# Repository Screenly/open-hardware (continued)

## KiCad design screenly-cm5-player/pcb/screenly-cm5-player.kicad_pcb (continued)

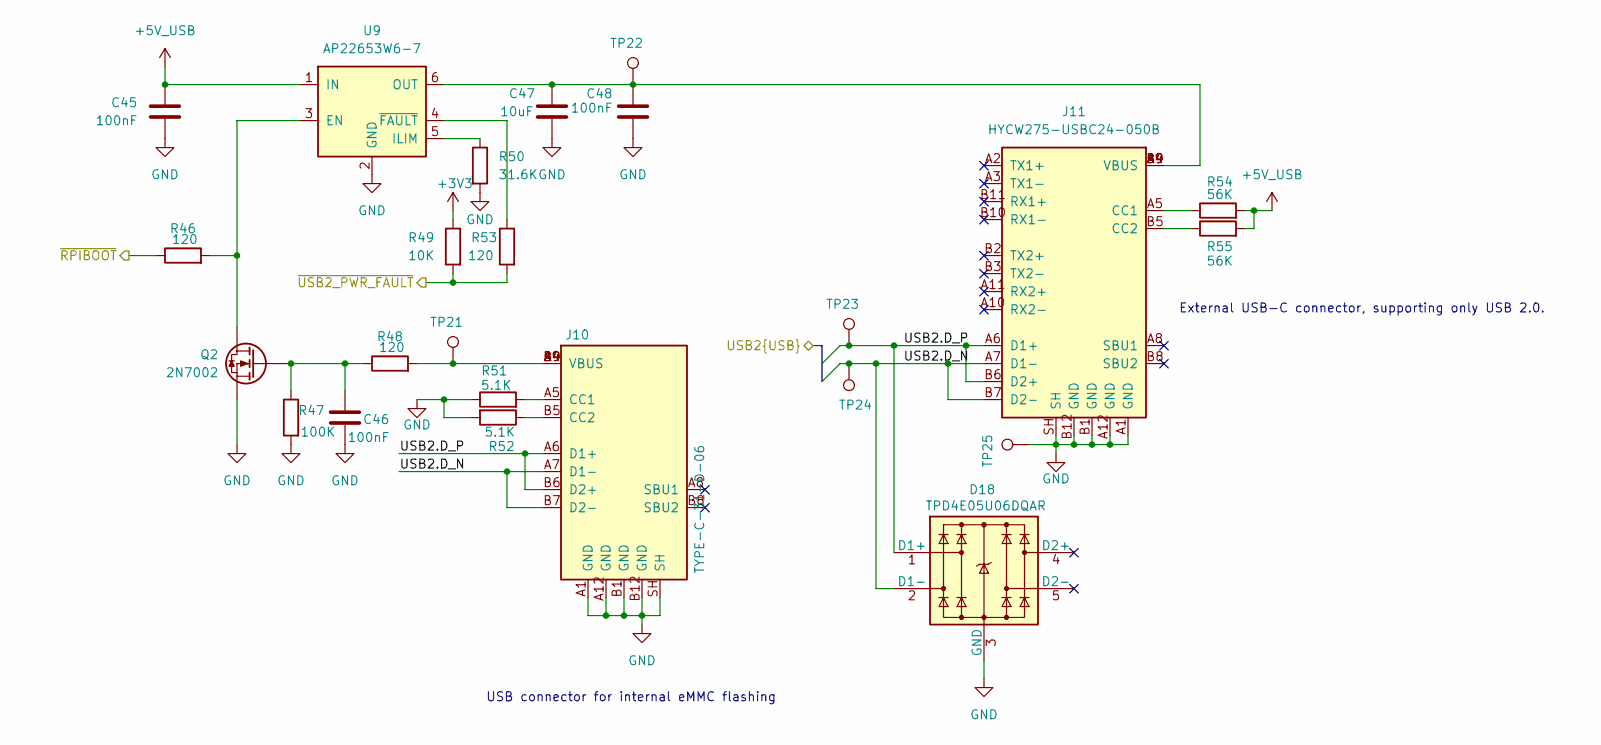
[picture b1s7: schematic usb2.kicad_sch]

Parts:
C45, C46, C48: 100nF; C_0402; tolerance 10%; voltage 50V; PartNumber SRLY-CAP-000001
C47: 10uF; C_1210; tolerance 10%; voltage 50V; PartNumber SRLY-CAP-000002
D18: TPD4E05U06DQAR; TI_USON-10_2.5x1.0mm_P0.5mm; PartNumber SRLY-DIO-000004
J10: TYPE-C-31-D-06; USB_C_Receptacle_HRO_TYPE-C-31-D-06_Vertical; voltage 5V; PartNumber SRLY-CON-000010
J11: HYCW275-USBC24-050B; USB_C_Receptacle_HOAUC_HYCW275-USBC24-050B; PartNumber SRLY-CON-000009
Q2: 2N7002; SOT-23; PartNumber SRLY-FET-000002
R46, R48, R53: 120; R_0402; tolerance 5%; voltage 50V; PartNumber SRLY-RES-000009
R47: 100K; R_0402; tolerance 1%; voltage 50V; PartNumber SRLY-RES-000004
R49: 10K; R_0402; tolerance 1%; voltage 50V; PartNumber SRLY-RES-000005
R50: 31.6K; R_0402; tolerance 1%; voltage 50V; PartNumber SRLY-RES-000010
R51, R52: 5.1K; R_0402; tolerance 1%; voltage 50V; PartNumber SRLY-RES-000012
R54, R55: 56K; R_0402; tolerance 1%; voltage 50V; PartNumber SRLY-RES-000013
TP21, TP22, TP23, TP24, TP25: TestPoint; TestPoint_Pad_D2.0mm
U9: AP22653W6-7; SOT-23-6; PartNumber SRLY-PWR-000003

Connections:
+3V3: R49.1; also elsewhere on the board
+5V_USB: C45.1, R54.2, R55.2, U9.1 (IN); also elsewhere on the board
/Compute Module/USB2.D_N: D18.2 (D1-), D18.9, J10.A7 (D1-), J10.B7 (D2-), J11.A7 (D1-), J11.B7 (D2-), TP24.1 (1_1); also elsewhere on the board
/Compute Module/USB2.D_P: D18.1 (D1+), D18.10, J10.A6 (D1+), J10.B6 (D2+), J11.A6 (D1+), J11.B6 (D2+), TP23.1 (1_1); also elsewhere on the board
/Compute Module/~RPIBOOT: R46.1; also elsewhere on the board
/Compute Module/~USB2_PWR_FAULT: R49.2, R53.2; also elsewhere on the board
GND: C45.2, C46.2, C47.2, C48.2, D18.3 (GND), D18.8 (GND), J10.A1 (GND), J10.A12 (GND), J10.B1 (GND), J10.B12 (GND), J10.SH, J11.A1 (GND), J11.A12 (GND), J11.B1 (GND), J11.B12 (GND), J11.SH, Q2.2 (S), R47.2, R50.2, R51.1, R52.2, TP25.1 (1_1), U9.2 (GND); also elsewhere on the board
unnamed: J10.A5 (CC1), R51.2
unnamed: J10.B5 (CC2), R52.1
unnamed: J10.A4 (VBUS), J10.A9 (VBUS), J10.B4 (VBUS), J10.B9 (VBUS), R48.2, TP21.1 (1_1)
unnamed: J11.A5 (CC1), R54.1
unnamed: J11.B5 (CC2), R55.1
unnamed: Q2.3 (D), R46.2, U9.3 (EN)
unnamed: C46.1, Q2.1 (G), R47.1, R48.1
unnamed: R50.1, U9.5 (ILIM)
unnamed: C47.1, C48.1, J11.A4 (VBUS), J11.A9 (VBUS), J11.B4 (VBUS), J11.B9 (VBUS), TP22.1 (1_1), U9.6 (OUT)
unnamed: R53.1, U9.4 (~FAULT)

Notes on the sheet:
External USB-C connector, supporting only USB 2.0.
USB connector for internal eMMC flashing

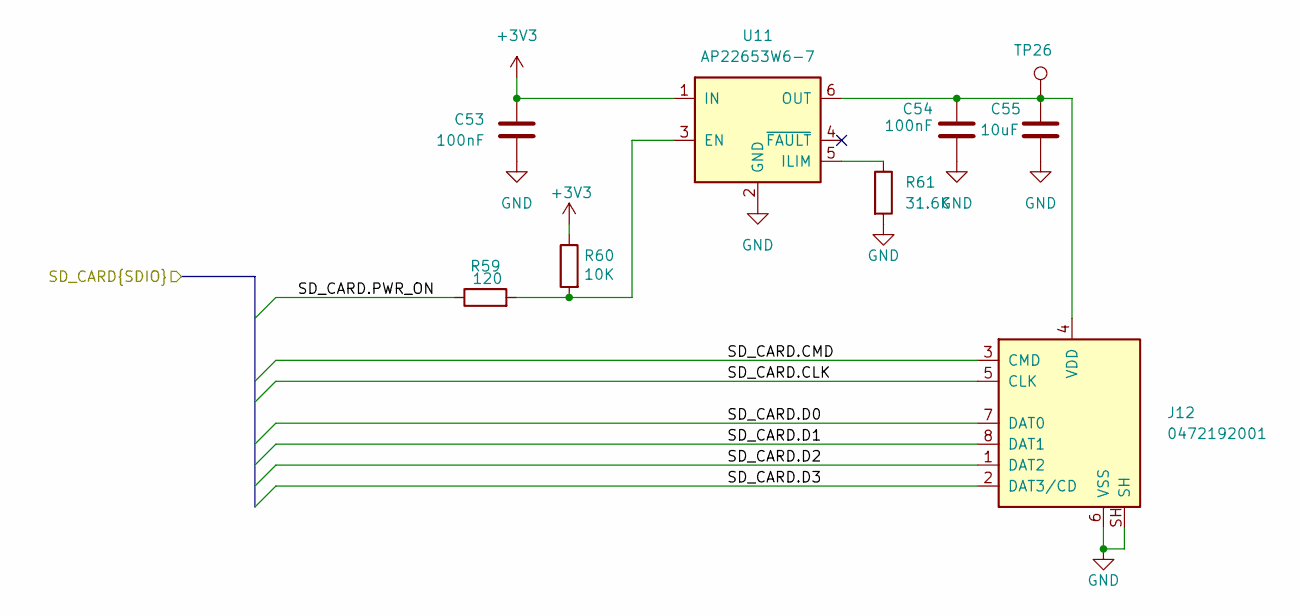
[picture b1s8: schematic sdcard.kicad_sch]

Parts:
C53, C54: 100nF; C_0402; tolerance 10%; voltage 50V; PartNumber SRLY-CAP-000001
C55: 10uF; C_1210; tolerance 10%; voltage 50V; PartNumber SRLY-CAP-000002
J12: 0472192001; microSD_HC_Molex_47219-2001; PartNumber SRLY-CON-000012
R59: 120; R_0402; tolerance 5%; voltage 50V; PartNumber SRLY-RES-000009
R60: 10K; R_0402; tolerance 1%; voltage 50V; PartNumber SRLY-RES-000005
R61: 31.6K; R_0402; tolerance 1%; voltage 50V; PartNumber SRLY-RES-000010
TP26: TestPoint; TestPoint_Pad_D2.0mm
U11: AP22653W6-7; SOT-23-6; PartNumber SRLY-PWR-000003

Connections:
+3V3: C53.1, R60.1, U11.1 (IN); also elsewhere on the board
/Compute Module/SD_CARD.CLK: J12.5 (CLK); also elsewhere on the board
/Compute Module/SD_CARD.CMD: J12.3 (CMD); also elsewhere on the board
/Compute Module/SD_CARD.D0: J12.7 (DAT0); also elsewhere on the board
/Compute Module/SD_CARD.D1: J12.8 (DAT1); also elsewhere on the board
/Compute Module/SD_CARD.D2: J12.1 (DAT2); also elsewhere on the board
/Compute Module/SD_CARD.D3: J12.2 (DAT3/CD); also elsewhere on the board
/Compute Module/SD_CARD.PWR_ON: R59.1; also elsewhere on the board
GND: C53.2, C54.2, C55.2, J12.6 (VSS), J12.SH, R61.2, U11.2 (GND); also elsewhere on the board
unnamed: C54.1, C55.1, J12.4 (VDD), TP26.1 (1_1), U11.6 (OUT)
unnamed: R59.2, R60.2, U11.3 (EN)
unnamed: R61.1, U11.5 (ILIM)

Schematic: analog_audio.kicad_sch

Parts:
C57, C62, C63, C66: 100nF; C_0402; tolerance 10%; voltage 50V; PartNumber SRLY-CAP-000001
C58, C59, C60, C61: 10uF; C_1210; tolerance 10%; voltage 50V; PartNumber SRLY-CAP-000002
C64, C65: 2.2uF; C_0603; tolerance 10%; voltage 16V; PartNumber SRLY-CAP-000009
C67, C68: 2.2nF; C_0402; tolerance 5%; voltage 50V; PartNumber SRLY-CAP-000010
J13: PJ-320A-4P; Jack_3.5mm_SHOUHAN_PJ-320A-4P_Horizontal; voltage 30V; PartNumber SRLY-CON-000013
R65: 10K; R_0402; tolerance 1%; voltage 50V; PartNumber SRLY-RES-000005
R66, R67: 470; R_0402; tolerance 5%; voltage 50V; PartNumber SRLY-RES-000001
U13: PCM5102APWR; TSSOP-20_4.4x6.5mm_P0.65mm; PartNumber SRLY-ITC-000003

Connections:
+3V3: C57.1, C58.1, C59.1, C61.1, C62.1, C66.1, R65.1, U13.1 (CPVDD), U13.8 (AVDD), U13.20 (DVDD); also elsewhere on the board
/Analog Audio/Audio.SCLK: U13.13 (BCK); also elsewhere on the board
/Analog Audio/Audio.SDO0: U13.14 (DIN); also elsewhere on the board
/Analog Audio/Audio.WS: U13.15 (LRCK); also elsewhere on the board
GND: C57.2, C58.2, C59.2, C60.2, C61.2, C62.2, C63.2, C65.2, C66.2, C67.1, C68.2, J13.A (S), J13.B (R2), U13.3 (CPGND), U13.9 (AGND), U13.10 (DEMP), U13.11 (FLT), U13.12 (SCK), U13.16 (FMT), U13.19 (DGND); also elsewhere on the board
unnamed: C68.1, J13.C (R1), R67.2
unnamed: C67.2, J13.D (T), R66.2
unnamed: C64.2, U13.4 (CAPM)
unnamed: C64.1, U13.2 (CAPP)
unnamed: C60.1, C63.1, U13.18 (LDOO)
unnamed: R66.1, U13.6 (OUTL)
unnamed: R67.1, U13.7 (OUTR)
unnamed: C65.1, U13.5 (VNEG)
unnamed: R65.2, U13.17 (XSMT)

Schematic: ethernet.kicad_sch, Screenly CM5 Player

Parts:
C18: 100nF; C_0402; tolerance 10%; voltage 50V; PartNumber SRLY-CAP-000001
D3, D4: TPD4E05U06DQAR; TI_USON-10_2.5x1.0mm_P0.5mm; PartNumber SRLY-DIO-000004
J4: HB-W01G0520DQW-R; RJ45_Hanbo_HB-W01G0520DQW-R_Horizontal; PartNumber SRLY-CON-000005
R19, R20: 470; R_0402; tolerance 5%; voltage 50V; PartNumber SRLY-RES-000001

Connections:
+3V3: J4.L1 (LED_GRN_A), J4.L4 (LED_YEL_A); also elsewhere on the board
/Compute Module/ETH.TRD0_N: D3.2 (D1-), D3.9, J4.3 (TD1-); also elsewhere on the board
/Compute Module/ETH.TRD0_P: D3.1 (D1+), D3.10, J4.2 (TD1+); also elsewhere on the board
/Compute Module/ETH.TRD1_N: D3.4 (D2+), D3.7, J4.7 (TD2-); also elsewhere on the board
/Compute Module/ETH.TRD1_P: D3.5 (D2-), D3.6, J4.4 (TD2+); also elsewhere on the board
/Compute Module/ETH.TRD2_N: D4.2 (D1-), D4.9, J4.6 (TD3-); also elsewhere on the board
/Compute Module/ETH.TRD2_P: D4.1 (D1+), D4.10, J4.5 (TD3+); also elsewhere on the board
/Compute Module/ETH.TRD3_N: D4.4 (D2+), D4.7, J4.9 (TD4-); also elsewhere on the board
/Compute Module/ETH.TRD3_P: D4.5 (D2-), D4.6, J4.8 (TD4+); also elsewhere on the board
/Compute Module/~ETH_LED_ACT: R20.2; also elsewhere on the board
/Compute Module/~ETH_LED_SPD: R19.2; also elsewhere on the board
GND: C18.2, D3.3 (GND), D3.8 (GND), D4.3 (GND), D4.8 (GND), J4.10 (CAP_GND), J4.SH (SHIELD); also elsewhere on the board
unnamed: C18.1, J4.1 (CT)
unnamed: J4.L2 (LED_GRN_K), R20.1
unnamed: J4.L3 (LED_YEL_K), R19.1

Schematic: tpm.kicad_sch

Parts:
C49, C50, C51: 100nF; C_0402; tolerance 10%; voltage 50V; PartNumber SRLY-CAP-000001
C52: 1uF; C_0402; tolerance 10%; voltage 25V; PartNumber SRLY-CAP-000007
R56, R57, R58: 10K; R_0402; tolerance 1%; voltage 50V; PartNumber SRLY-RES-000005
U10: SLB9672XU20FW1624; Infineon_PG-UQFN-32-1_5x5mm_P0.5mm_EP3.6x3.6mm; PartNumber SRLY-ITC-000002

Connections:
+3V3: C49.1, C50.1, C51.1, C52.1, R56.1, R57.1, U10.1 (VDD), U10.8 (NCI/VDD), U10.14 (VDD), U10.22 (VDD); also elsewhere on the board
/Compute Module/TPM.CLK: U10.19 (SCLK); also elsewhere on the board
/Compute Module/TPM.MISO: U10.24 (MISO); also elsewhere on the board
/Compute Module/TPM.MOSI: U10.21 (MOSI); also elsewhere on the board
/Compute Module/TPM.~CS: R57.2, U10.20 (~CS); also elsewhere on the board
/Compute Module/~TPM_PIRQ: R56.2, U10.18 (~PIRQ); also elsewhere on the board
/Compute Module/~TPM_RST: R58.1, U10.17 (~RST); also elsewhere on the board
GND: C49.2, C50.2, C51.2, C52.2, R58.2, U10.2 (GND), U10.9 (GND), U10.16 (NCI/GND), U10.23 (GND), U10.32 (GND), U10.33 (GND); also elsewhere on the board

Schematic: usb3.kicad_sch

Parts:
C35, C36, C37, C38, C41, C42: 100nF; C_0402; tolerance 10%; voltage 50V; PartNumber SRLY-CAP-000001
C39, C40: 10uF; C_1210; tolerance 10%; voltage 50V; PartNumber SRLY-CAP-000002
D11, D12, D13, D14: TPD4E05U06DQAR; TI_USON-10_2.5x1.0mm_P0.5mm; PartNumber SRLY-DIO-000004
J8, J9: USB-A3-S-RA; USB_A_USB3_AdamTech_USB-A3-S-RA_Horizontal; voltage 30V; PartNumber SRLY-CON-000011
R33, R34: 100K; R_0402; tolerance 1%; voltage 50V; PartNumber SRLY-RES-000004
R35, R36, R37, R38: 10K; R_0402; tolerance 1%; voltage 50V; PartNumber SRLY-RES-000005
R39, R40: 120; R_0402; tolerance 5%; voltage 50V; PartNumber SRLY-RES-000009
TP15, TP16: TestPoint; TestPoint_Pad_D2.0mm
U7, U8: AP22653W6-7; SOT-23-6; PartNumber SRLY-PWR-000003

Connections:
+3V3: R35.1, R36.1; also elsewhere on the board
+5V_USB: C35.1, C36.1, U7.1 (IN), U8.1 (IN); also elsewhere on the board
/Compute Module/USB3_0.D_N: D13.2 (D1-), D13.9, J8.2 (D-); also elsewhere on the board
/Compute Module/USB3_0.D_P: D13.1 (D1+), D13.10, J8.3 (D+); also elsewhere on the board
/Compute Module/USB3_0.RX_N: D11.5 (D2-), D11.6, J8.5 (SSRX-); also elsewhere on the board
/Compute Module/USB3_0.RX_P: D11.4 (D2+), D11.7, J8.6 (SSRX+); also elsewhere on the board
/Compute Module/USB3_0.TX_N: D11.2 (D1-), D11.9, J8.8 (SSTX-); also elsewhere on the board
/Compute Module/USB3_0.TX_P: D11.1 (D1+), D11.10, J8.9 (SSTX+); also elsewhere on the board
/Compute Module/USB3_1.D_N: D14.2 (D1-), D14.9, J9.2 (D-); also elsewhere on the board
/Compute Module/USB3_1.D_P: D14.1 (D1+), D14.10, J9.3 (D+); also elsewhere on the board
/Compute Module/USB3_1.RX_N: D12.5 (D2-), D12.6, J9.5 (SSRX-); also elsewhere on the board
/Compute Module/USB3_1.RX_P: D12.4 (D2+), D12.7, J9.6 (SSRX+); also elsewhere on the board
/Compute Module/USB3_1.TX_N: D12.2 (D1-), D12.9, J9.8 (SSTX-); also elsewhere on the board
/Compute Module/USB3_1.TX_P: D12.1 (D1+), D12.10, J9.9 (SSTX+); also elsewhere on the board
/Compute Module/VBUS_EN: C37.1, C38.1, R33.1, R34.1, U7.3 (EN), U8.3 (EN); also elsewhere on the board
/Compute Module/~USB3_0_PWR_FAULT: R35.2, R39.2; also elsewhere on the board
/Compute Module/~USB3_1_PWR_FAULT: R36.2, R40.2; also elsewhere on the board
GND: C35.2, C36.2, C37.2, C38.2, C39.2, C40.2, C41.2, C42.2, D11.3 (GND), D11.8 (GND), D12.3 (GND), D12.8 (GND), D13.3 (GND), D13.8 (GND), D14.3 (GND), D14.8 (GND), J8.4 (GND), J8.7 (GND_DRAIN), J8.SH, J9.4 (GND), J9.7 (GND_DRAIN), J9.SH, R33.2, R34.2, R37.2, R38.2, U7.2 (GND), U8.2 (GND); also elsewhere on the board
unnamed: C39.1, C41.1, J8.1 (VBUS), TP15.1 (1_1), U7.6 (OUT)
unnamed: C40.1, C42.1, J9.1 (VBUS), TP16.1 (1_1), U8.6 (OUT)
unnamed: R37.1, U7.5 (ILIM)
unnamed: R39.1, U7.4 (~FAULT)
unnamed: R38.1, U8.5 (ILIM)
unnamed: R40.1, U8.4 (~FAULT)

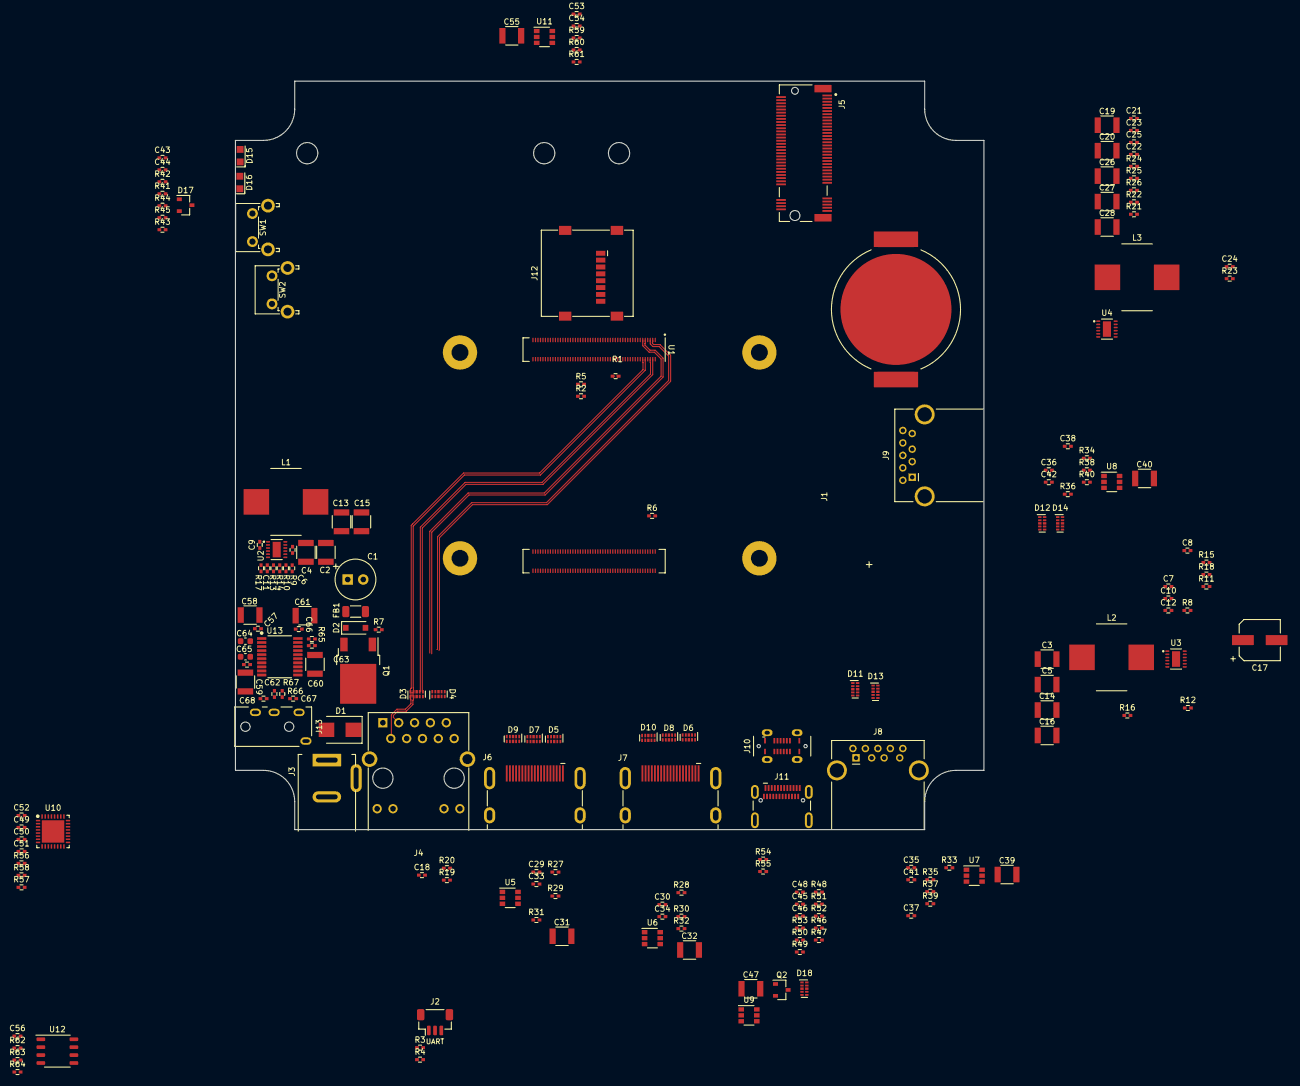
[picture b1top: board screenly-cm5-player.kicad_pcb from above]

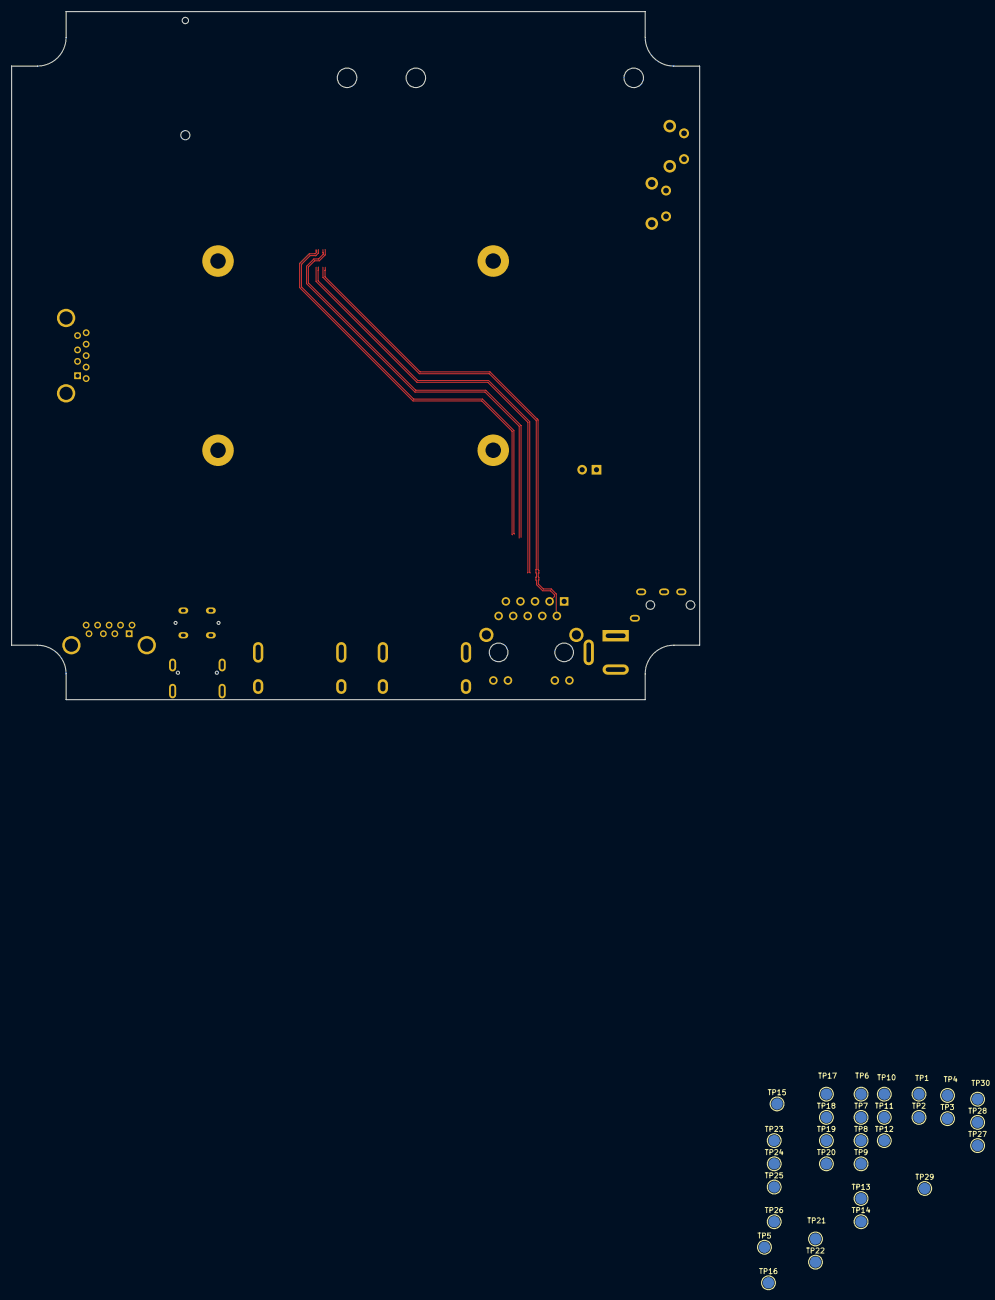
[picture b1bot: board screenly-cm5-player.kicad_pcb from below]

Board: 4 copper layers, 120.0 x 120.0 mm, 220 parts (30 on the bottom side), 166 nets.

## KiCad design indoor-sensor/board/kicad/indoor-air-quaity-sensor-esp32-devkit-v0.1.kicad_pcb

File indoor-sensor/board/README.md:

# Indoor Air Quality Sensor – XIAO ESP32S3 & CJMCU-6668

This repository contains the hardware design files for a compact Indoor Air Quality Sensor based on the Seeed Studio XIAO ESP32S3 and the CJMCU-6668 environmental sensor module (ENS160 + BME280).

## Main Components

| Part | Description |
|------|-------------|
| XIAO ESP32S3 | Primary MCU module (WiFi + BLE) |
| CJMCU-6668 | ENS160 + BME280 environmental sensor |
| I²C Pull-ups | 4.7kΩ resistors (if required) |
| Connector Headers | XIAO pin headers, sensor headers |
| Power Supply | USB-C (via XIAO) |
| Mounting Hardware | Optional standoffs and enclosure |

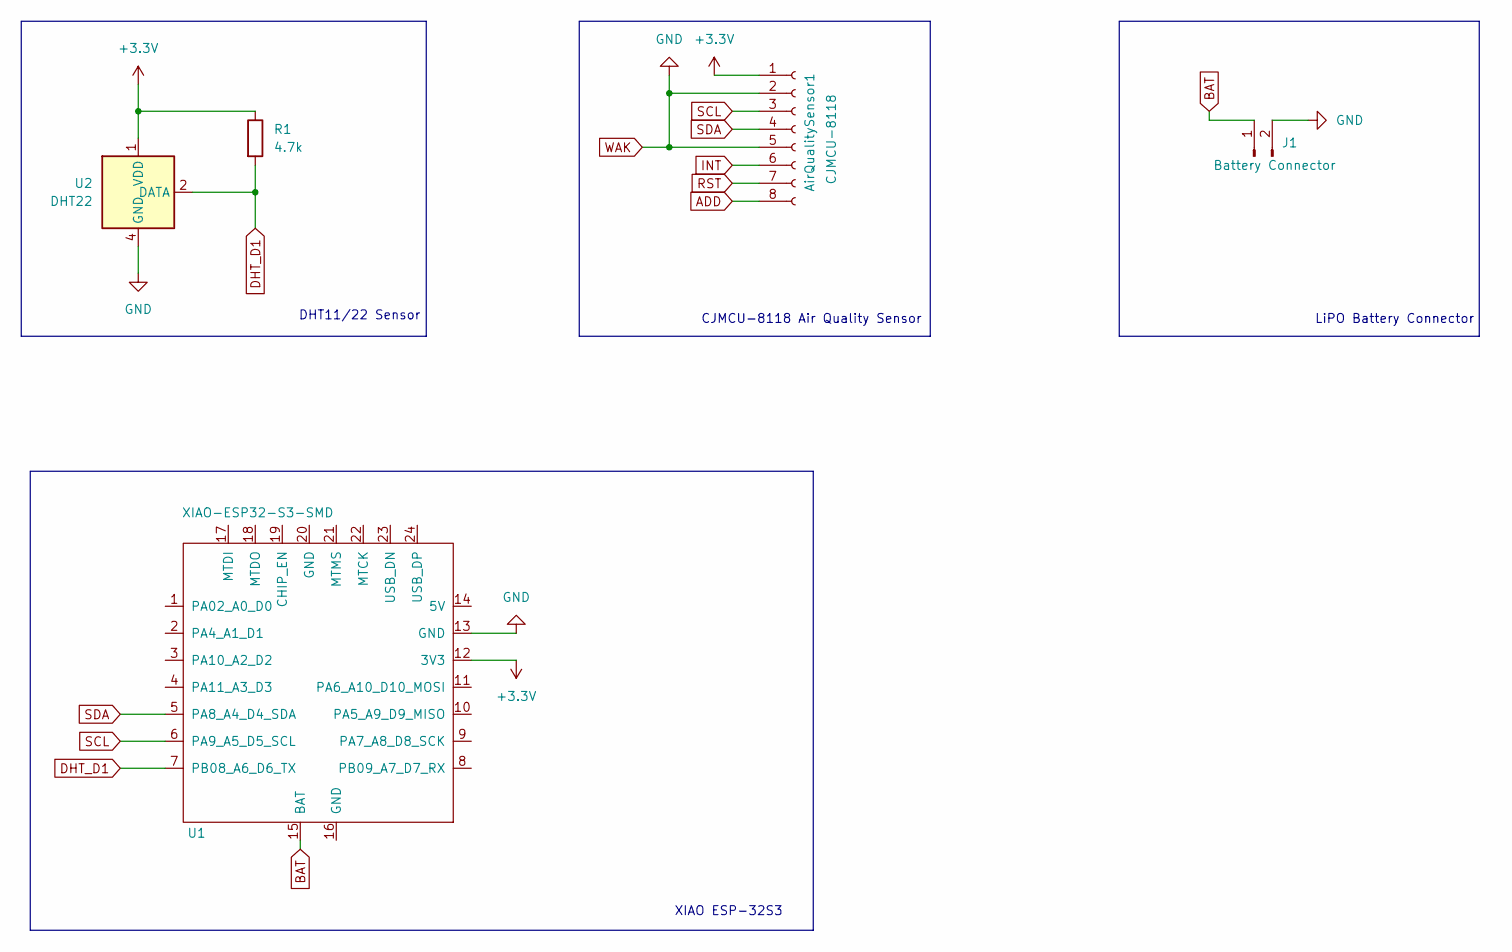
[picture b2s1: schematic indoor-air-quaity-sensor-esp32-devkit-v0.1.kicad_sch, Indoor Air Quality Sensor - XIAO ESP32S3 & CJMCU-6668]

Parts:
AirQualitySensor1: CJMCU-8118; PinHeader_1x08_P2.54mm_Vertical
J1: Battery Connector; PinHeader_1x02_P2.54mm_Vertical
R1: 4.7k; R_Axial_DIN0204_L3.6mm_D1.6mm_P5.08mm_Horizontal
U1: XIAO-ESP32-S3-SMD
U2: DHT22; Aosong_DHT11_5.5x12.0_P2.54mm

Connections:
+3.3V: AirQualitySensor1.1, R1.1, U1.12 (3V3), U2.1 (VDD)
ADD: AirQualitySensor1.8
BAT: J1.1, U1.15 (BAT)
DHT_D1: R1.2, U1.7 (PB08_A6_D6_TX), U2.2 (DATA)
INT: AirQualitySensor1.6
RST: AirQualitySensor1.7
SCL: AirQualitySensor1.3, U1.6 (PA9_A5_D5_SCL)
SDA: AirQualitySensor1.4, U1.5 (PA8_A4_D4_SDA)
WAK: AirQualitySensor1.2, AirQualitySensor1.5, J1.2, U1.13 (GND), U2.4 (GND)

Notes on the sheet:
DHT11/22 Sensor
XIAO ESP-32S3
CJMCU-8118 Air Quality Sensor
LiPO Battery Connector

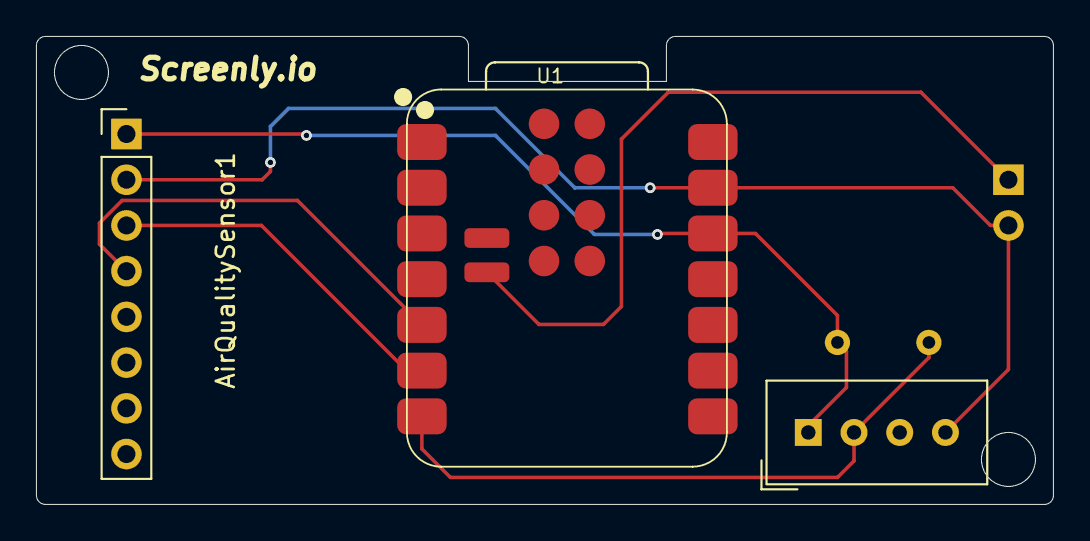
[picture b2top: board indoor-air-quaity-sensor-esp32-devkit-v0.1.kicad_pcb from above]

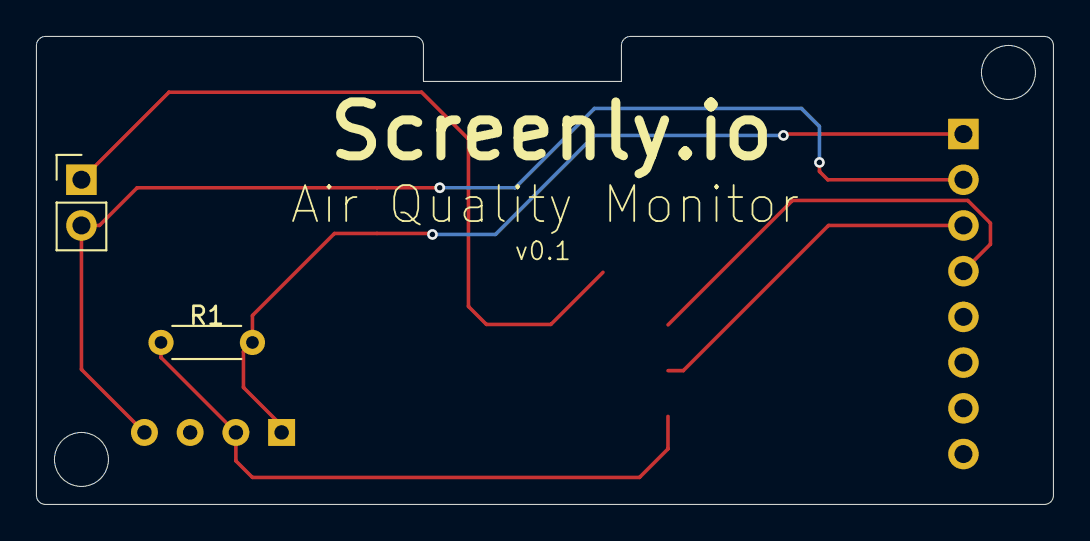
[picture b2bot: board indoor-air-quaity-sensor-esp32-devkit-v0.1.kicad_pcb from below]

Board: 2 copper layers, 56.5 x 26.0 mm, 5 parts (2 on the bottom side), 6 nets.

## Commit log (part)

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2025-05-05 Adds initial draft
2025-12-08 add kicad pcb files
